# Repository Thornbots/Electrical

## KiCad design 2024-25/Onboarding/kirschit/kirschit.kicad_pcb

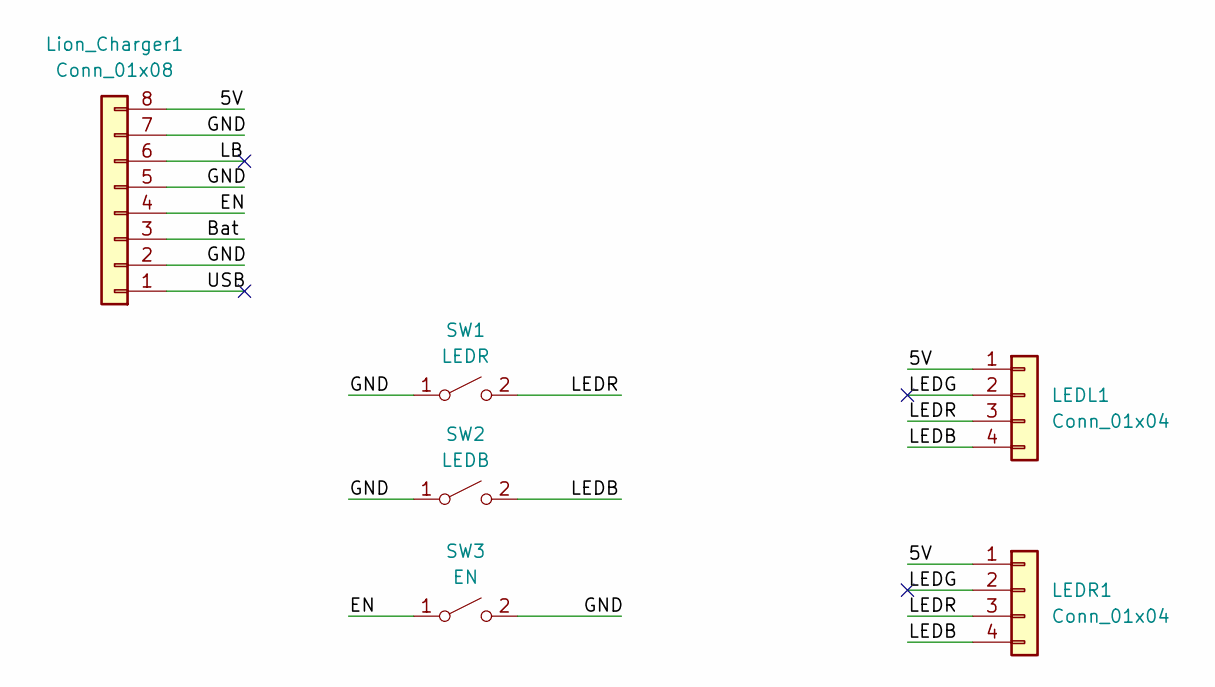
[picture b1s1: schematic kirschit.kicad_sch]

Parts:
LEDL1: Conn_01x04; PinSocket_1x04_P2.54mm_Vertical
LEDR1: Conn_01x04; PinSocket_1x04_P2.54mm_Vertical
Lion_Charger1: Conn_01x08; PinSocket_1x08_P2.54mm_Vertical
SW1: LEDR; SW_RB141C1100
SW2: LEDB; SW_RB141C1100
SW3: EN; SW_RB141C1100

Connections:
/5V: LEDL1.1, LEDR1.1, Lion_Charger1.8
/Bat: Lion_Charger1.3
/EN: Lion_Charger1.4, SW3.1 (A)
/GND: Lion_Charger1.2, Lion_Charger1.5, Lion_Charger1.7, SW1.1 (A), SW2.1 (A), SW3.2 (B)
/LB: Lion_Charger1.6
/LEDB: LEDL1.4, LEDR1.4, SW2.2 (B)
/LEDG: LEDL1.2, LEDR1.2
/LEDR: LEDL1.3, LEDR1.3, SW1.2 (B)
/USB: Lion_Charger1.1

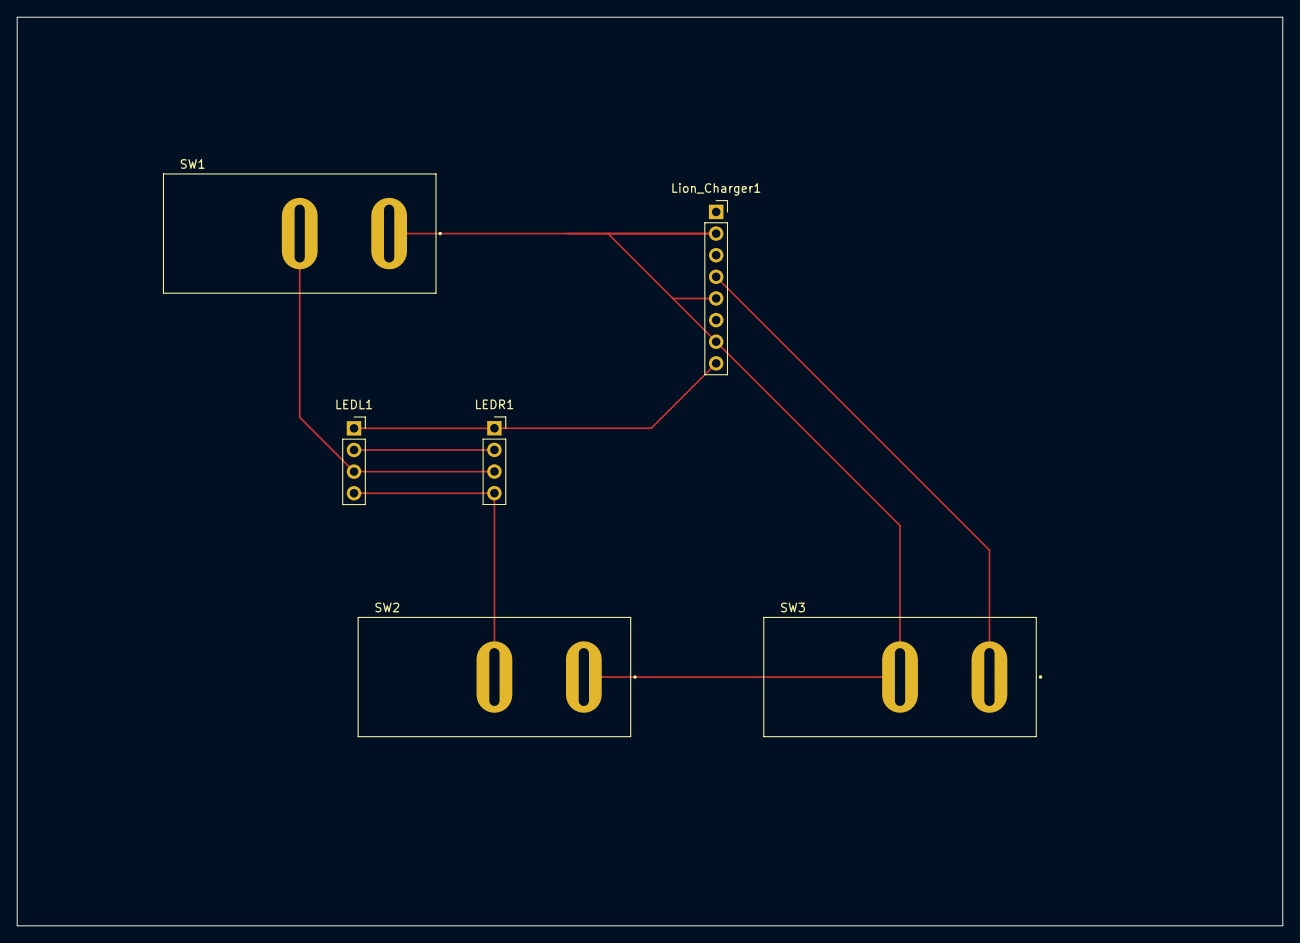
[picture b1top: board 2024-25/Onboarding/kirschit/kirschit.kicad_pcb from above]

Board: 2 copper layers, 148.6 x 106.7 mm, 6 parts (0 on the bottom side), 6 nets.

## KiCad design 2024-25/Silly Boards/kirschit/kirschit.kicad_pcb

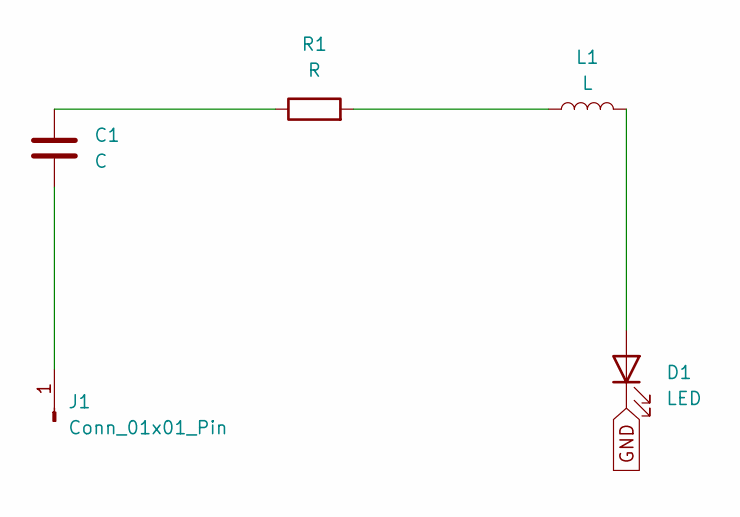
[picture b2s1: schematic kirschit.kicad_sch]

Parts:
C1: C; C_Elec_3x5.4
D1: LED; LED_D3.0mm_Horizontal_O3.81mm_Z6.0mm
J1: Conn_01x01_Pin; PinHeader_1x01_P2.54mm_Vertical
L1: L; L_Axial_L5.3mm_D2.2mm_P7.62mm_Horizontal_Vishay_IM-1
R1: R; R_Axial_DIN0414_L11.9mm_D4.5mm_P15.24mm_Horizontal

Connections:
GND: D1.1 (K)
unnamed: C1.1, R1.1
unnamed: D1.2 (A), L1.2
unnamed: C1.2, J1.1
unnamed: L1.1, R1.2

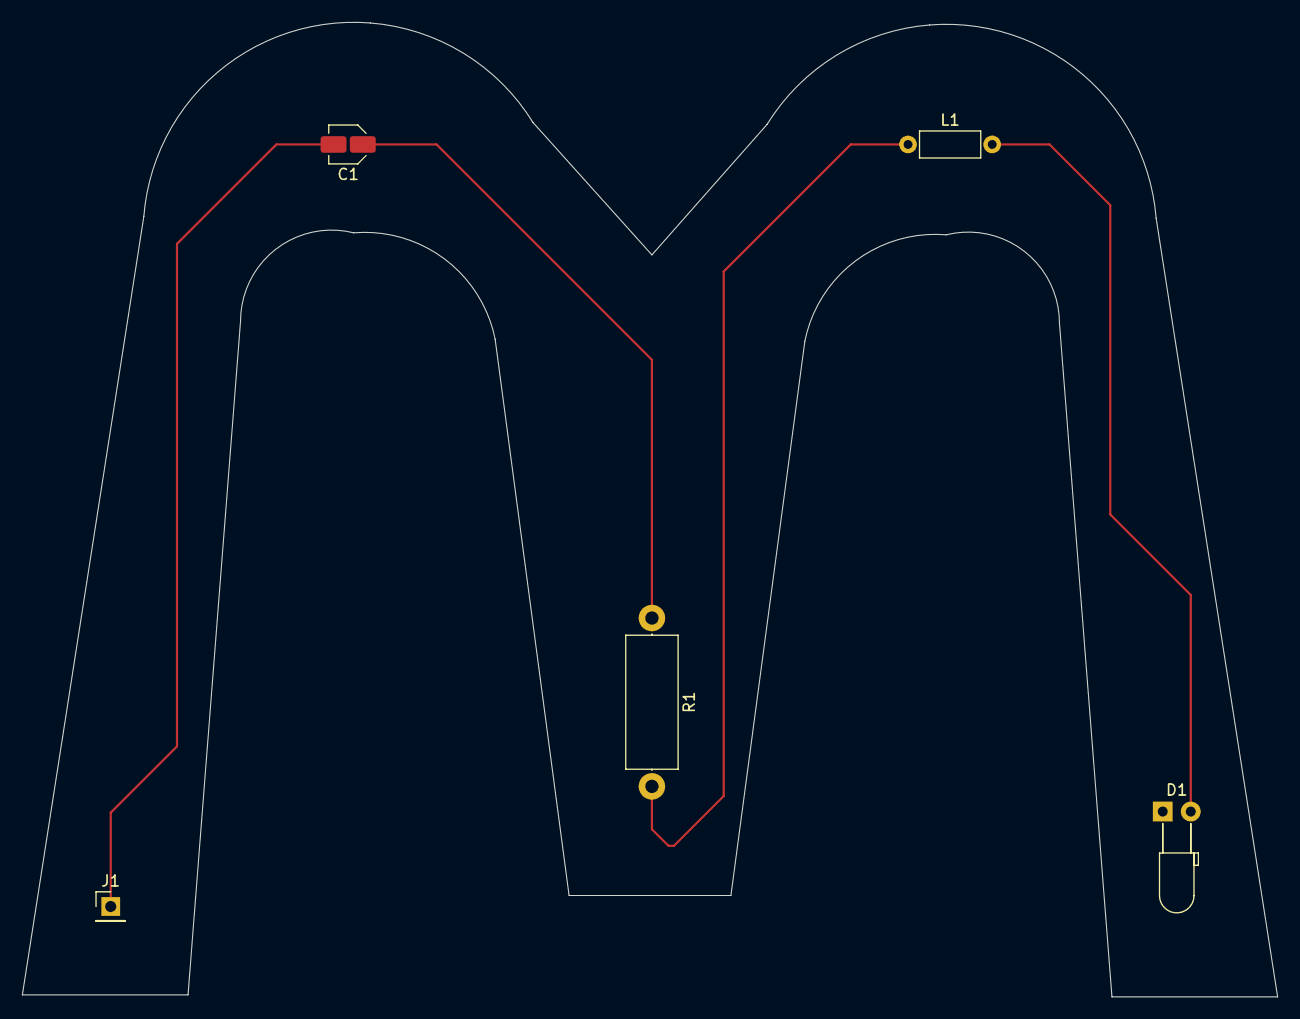
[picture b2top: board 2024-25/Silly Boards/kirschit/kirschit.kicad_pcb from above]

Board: 2 copper layers, 113.7 x 88.2 mm, 5 parts (0 on the bottom side), 4 nets.

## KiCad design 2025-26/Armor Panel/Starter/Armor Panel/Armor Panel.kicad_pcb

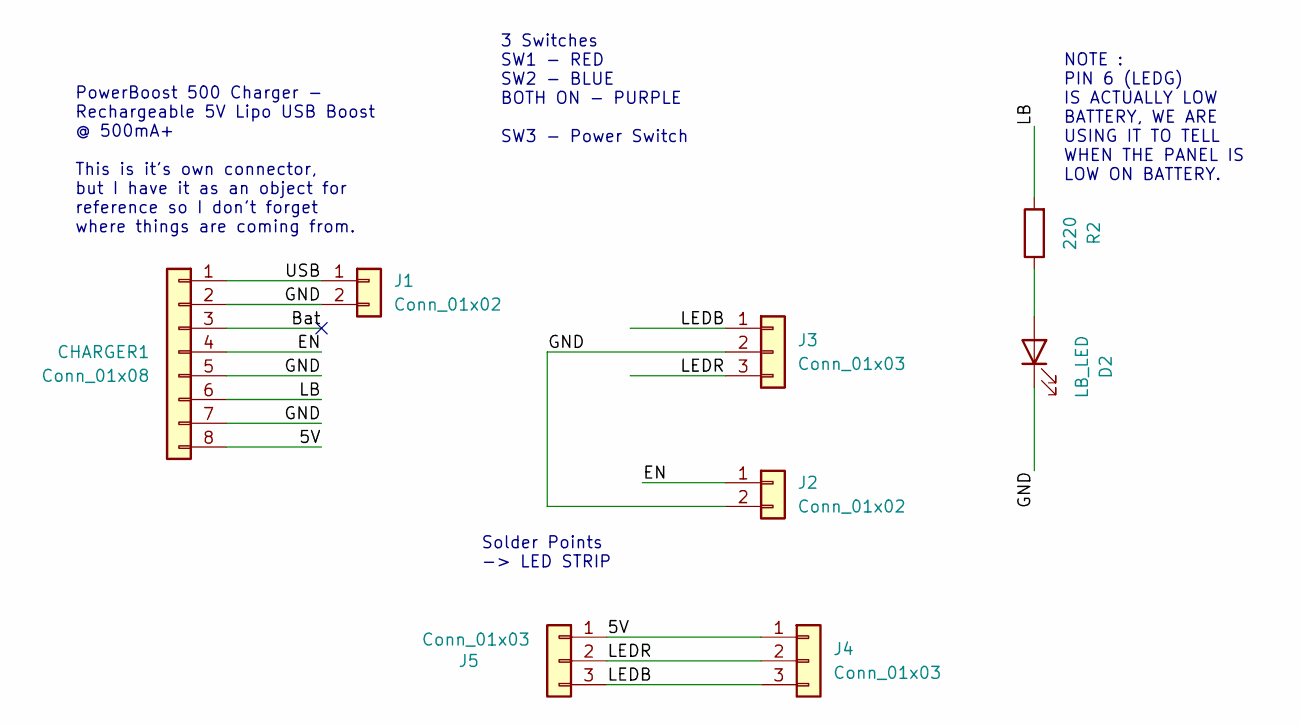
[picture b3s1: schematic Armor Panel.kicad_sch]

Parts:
CHARGER1: Conn_01x08; Power Boost Board
D2: LB_LED; LED_D5.0mm
J1, J2: Conn_01x02; JST_PH_B2B-PH-K_1x02_P2.00mm_Vertical
J3, J4, J5: Conn_01x03; JST_PH_B3B-PH-K_1x03_P2.00mm_Vertical
R2: 220; R_Axial_DIN0309_L9.0mm_D3.2mm_P12.70mm_Horizontal

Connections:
/5V: CHARGER1.8, J4.1, J5.1
/Bat: CHARGER1.3
/EN: CHARGER1.4, J2.1
/GND: CHARGER1.2, CHARGER1.5, CHARGER1.7, D2.1 (K), J1.2, J2.2, J3.2
/LB: CHARGER1.6, R2.2
/LEDB: J3.1, J4.3, J5.3
/LEDR: J3.3, J4.2, J5.2
/USB: CHARGER1.1, J1.1
unnamed: D2.2 (A), R2.1

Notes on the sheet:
PowerBoost 500 Charger - Rechargeable 5V Lipo USB Boost @ 500mA+ This is it's own connector, but I have it as an object for reference so I don't forget where things are coming from.
Solder Points -> LED STRIP
3 Switches SW1 - RED SW2 - BLUE BOTH ON - PURPLE SW3 - Power Switch
NOTE : PIN 6 (LEDG) IS ACTUALLY LOW BATTERY, WE ARE USING IT TO TELL WHEN THE PANEL IS LOW ON BATTERY.

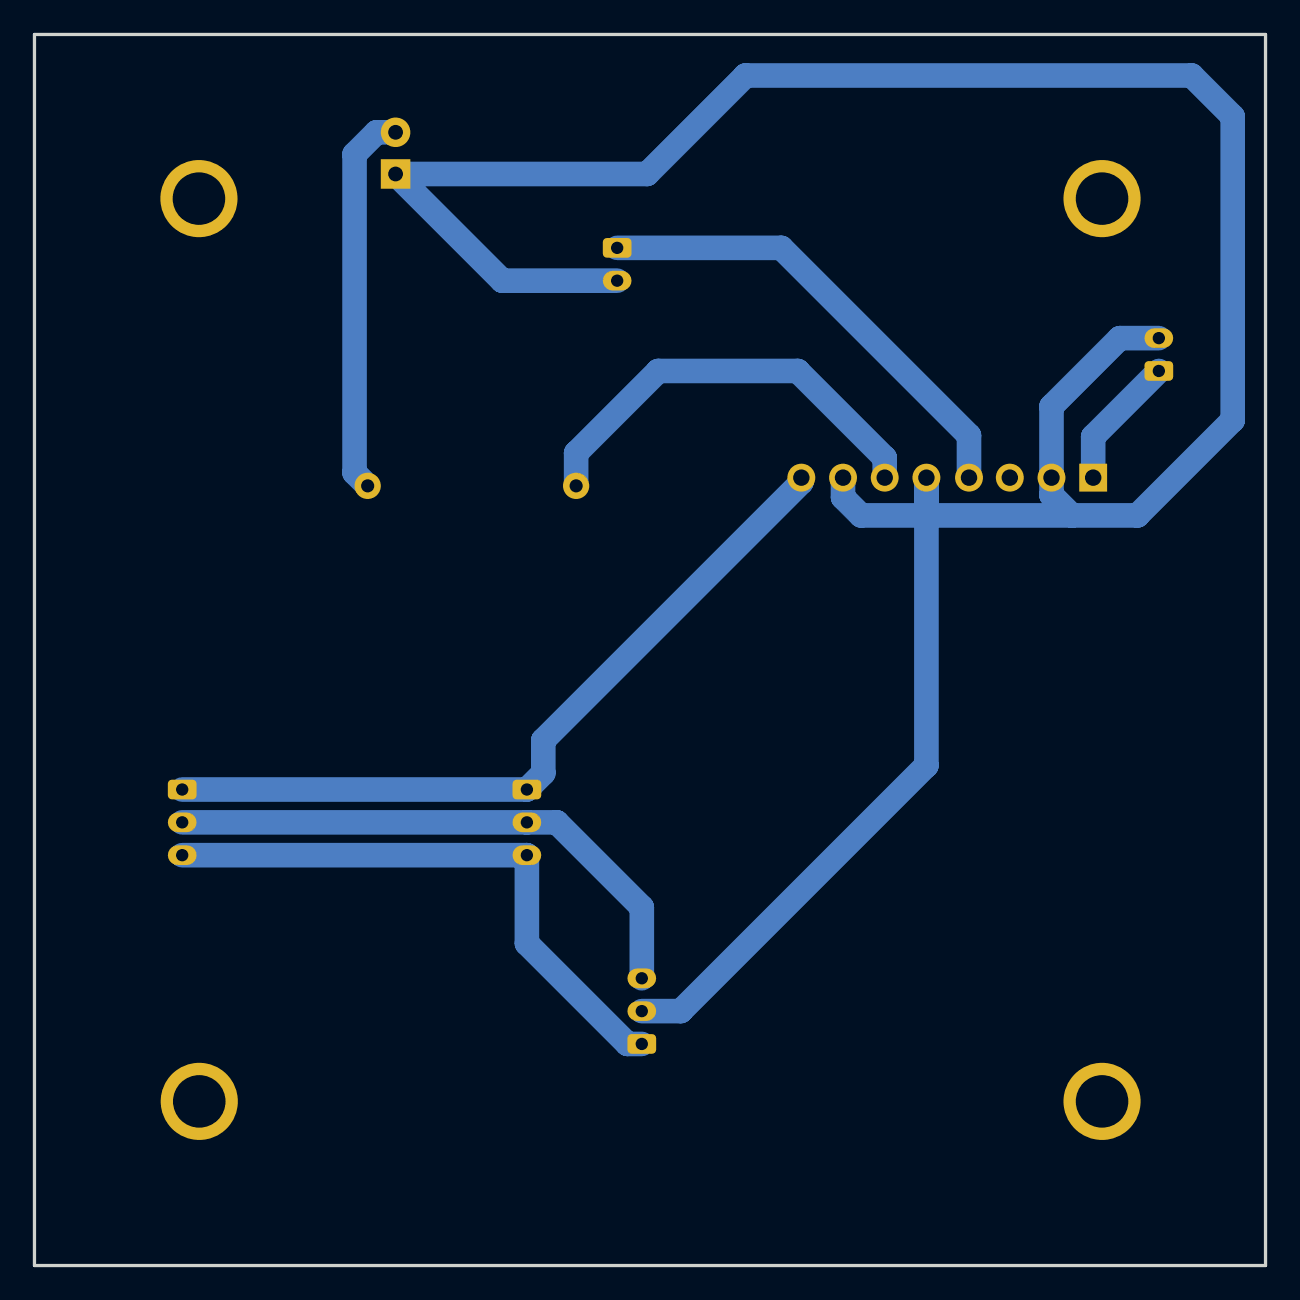
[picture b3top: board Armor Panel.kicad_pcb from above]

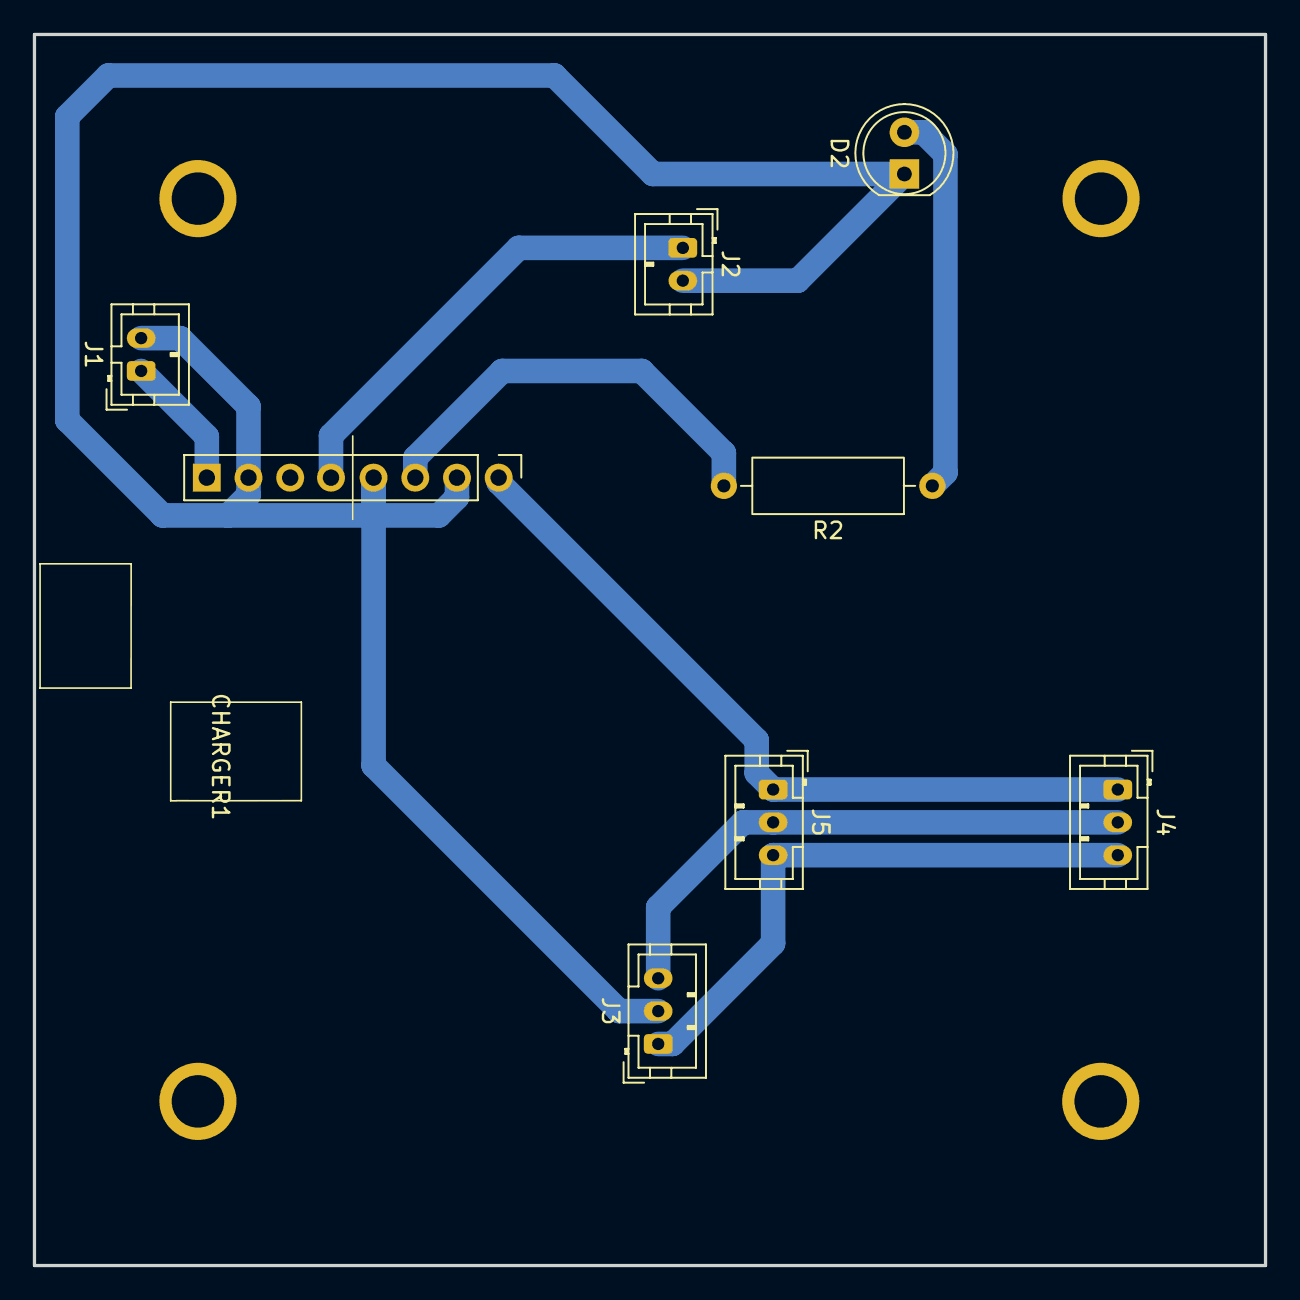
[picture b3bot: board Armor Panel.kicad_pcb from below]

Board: 2 copper layers, 75.0 x 75.0 mm, 8 parts (8 on the bottom side), 8 nets.

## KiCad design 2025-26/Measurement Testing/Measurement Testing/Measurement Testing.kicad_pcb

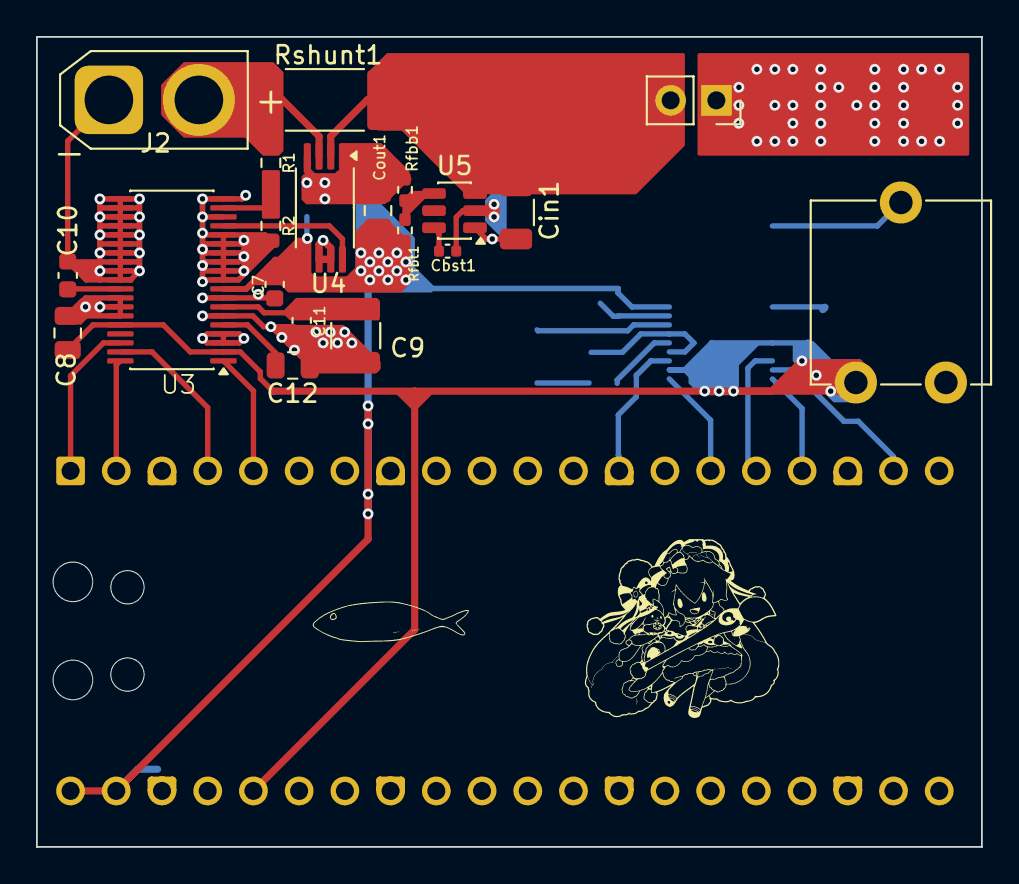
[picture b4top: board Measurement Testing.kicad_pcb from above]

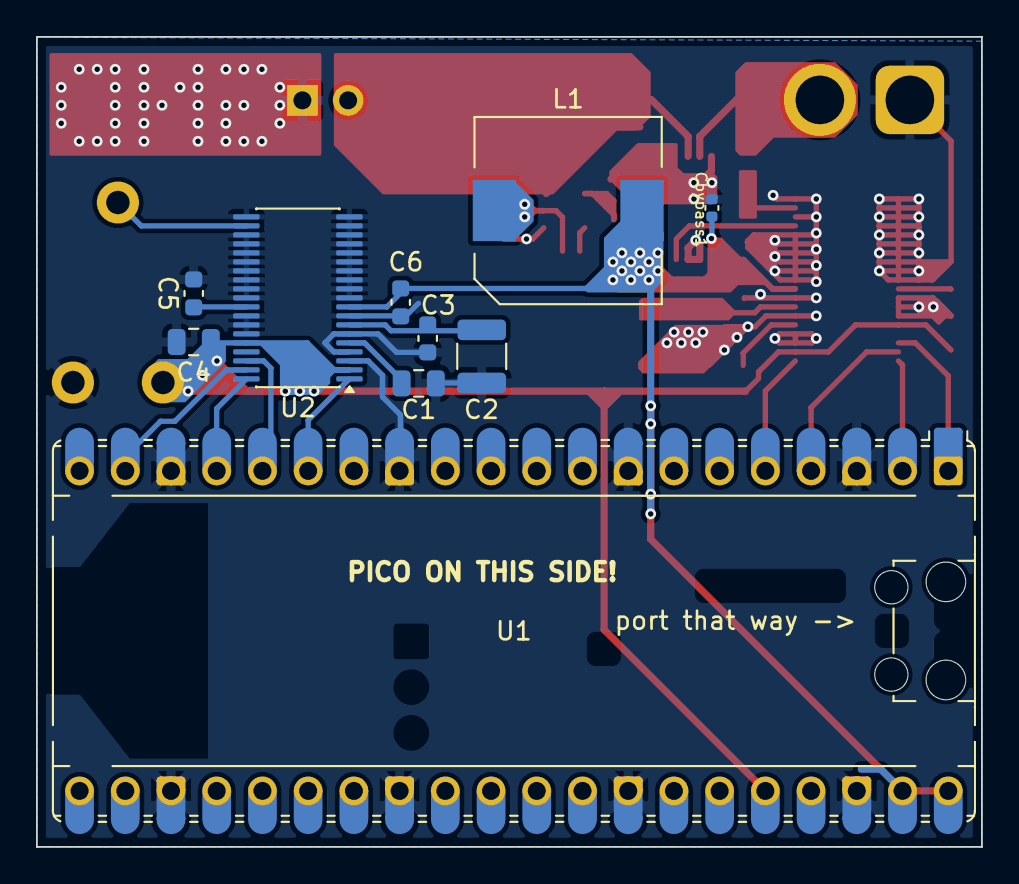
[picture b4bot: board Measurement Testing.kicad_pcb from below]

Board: 2 copper layers, 52.5 x 45.0 mm, 30 parts (10 on the bottom side), 25 nets.

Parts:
C1, C4, C8, C12: 10 uF; C_0805_2012Metric
C2, C9: 22 uF; C_1210_3225Metric
C3, C5, C6, C7, C10, C11: 1 uF; C_0603_1608Metric
Cbst1: 100n; C_0402_1005Metric
Cbypass1: 100n; C_0402_1005Metric
Cin1: 10u; C_1206_3216Metric
Cout1: 47u; C_0805_2012Metric
J1: Power Supply; PinSocket_1x02_P2.54mm_Vertical
J2: XT30PW-F; AMASS_XT30U-F_1x02_P5.0mm_Vertical
L1: 13u; L_Wuerth_WE-PDF
R1: 8.2k; R_0603_1608Metric
R2: 1k; R_0603_1608Metric
RV1: R_Potentiometer; Potentiometer_ACP_CA9-V10_Vertical
Rfbb1: 13.7k; R_0402_1005Metric_Pad0.72x0.64mm_HandSolder
Rfbt1: 100k; R_0402_1005Metric_Pad0.72x0.64mm_HandSolder
Rshunt1: 5m; R_2512_6332Metric
U1: RASPBERRY_PI_PICO; RaspberryPi_Pico_Common_Unspecified
U2, U3: ADS8684IDBTR; TSSOP-38_4.4x9.7mm_P0.5mm
U4: INA240A2PWR; TSSOP-8_4.4x3mm_P0.65mm
U5: TPS54308DDCR; SOT-23-6

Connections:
3V3: C4.1, C8.1, RV1.3, U1.36 (3V3), U2.2 (~RST/~PD), U2.34 (DVDD), U3.2 (~RST/~PD), U3.34 (DVDD)
5V: C6.1, C7.1, Cbypass1.2, Cout1.1, L1.2, Rfbt1.1, U1.39 (VSYS), U1.40 (VBUS), U2.9 (AVDD), U3.9 (AVDD), U4.5
GND: C1.2, C2.2, C3.2, C4.2, C5.2, C6.2, C7.2, C8.2, C9.2, C10.2, C11.2, C12.2, Cbypass1.1, Cin1.2, Cout1.2, J1.1, J2.1, R2.2, RV1.1, Rfbb1.2, U1.3 (GND), U1.8 (GND), U1.13 (GND), U1.18 (GND), U1.23 (GND), U1.28 (GND), U1.33 (AGND), U1.38 (GND), U2.3 (DAISY), U2.4 (~REFSEL), U2.6 (REFGND), U2.8 (AGND), U2.10 (AUX_IN), U2.11 (AUX_GND), U2.12 (NC), U2.13 (NC__1), U2.14 (NC__2), U2.15 (NC__3), U2.16 (AIN_0P), U2.17 (AIN_0GND), U2.18 (AIN_1P), U2.19 (AIN_1GND), U2.20 (AIN_2GND), U2.22 (AIN_3GND), U2.23 (AIN_3P), U2.24 (NC__4), U2.25 (NC__5), U2.26 (NC__6), U2.27 (NC__7), U2.28 (AGND__1), U2.29 (AGND__2), U2.31 (AGND__3), U2.32 (AGND__4), U2.33 (DGND), U3.3 (DAISY), U3.4 (~REFSEL), U3.6 (REFGND), U3.8 (AGND), U3.10 (AUX_IN), U3.11 (AUX_GND), U3.12 (NC), U3.13 (NC__1), U3.14 (NC__2), U3.15 (NC__3), U3.17 (AIN_0GND), U3.19 (AIN_1GND), U3.20 (AIN_2GND), U3.21 (AIN_2P), U3.22 (AIN_3GND), U3.23 (AIN_3P), U3.24 (NC__4), U3.25 (NC__5), U3.26 (NC__6), U3.27 (NC__7), U3.28 (AGND__1), U3.29 (AGND__2), U3.31 (AGND__3), U3.32 (AGND__4), U3.33 (DGND), U4.1, U4.4, U4.6, U4.7, U5.1 (GND)
unnamed: J2.2, R1.1, Rshunt1.2, U4.3
unnamed: U1.1 (GPIO0), U3.36 (SDO)
unnamed: U1.2 (GPIO1), U3.38 (~CS)
unnamed: U1.4 (GPIO2), U3.37 (SCLK)
unnamed: U1.5 (GPIO3), U3.1 (SDI)
unnamed: U1.15 (GPIO11), U2.1 (SDI)
unnamed: U1.16 (GPIO12), U2.36 (SDO)
unnamed: U1.17 (GPIO13), U2.38 (~CS)
unnamed: U1.19 (GPIO14), U2.37 (SCLK)
unnamed: RV1.2, U2.21 (AIN_2P)
unnamed: C5.1, U2.30 (AVDD__1)
unnamed: C2.1, C3.1, U2.7 (REFCAP)
unnamed: C1.1, U2.5 (REFIO)
unnamed: U3.16 (AIN_0P), U4.8
unnamed: R1.2, R2.1, U3.18 (AIN_1P)
unnamed: C10.1, U3.30 (AVDD__1)
unnamed: C9.1, C11.1, U3.7 (REFCAP)
unnamed: C12.1, U3.5 (REFIO)
unnamed: Cbst1.1, U5.6 (BOOT)
unnamed: Rfbb1.1, Rfbt1.2, U5.4 (FB)
unnamed: Cbst1.2, L1.1, U5.2 (SW)
VIN: Cin1.1, J1.2, Rshunt1.1, U4.2, U5.3 (VIN)

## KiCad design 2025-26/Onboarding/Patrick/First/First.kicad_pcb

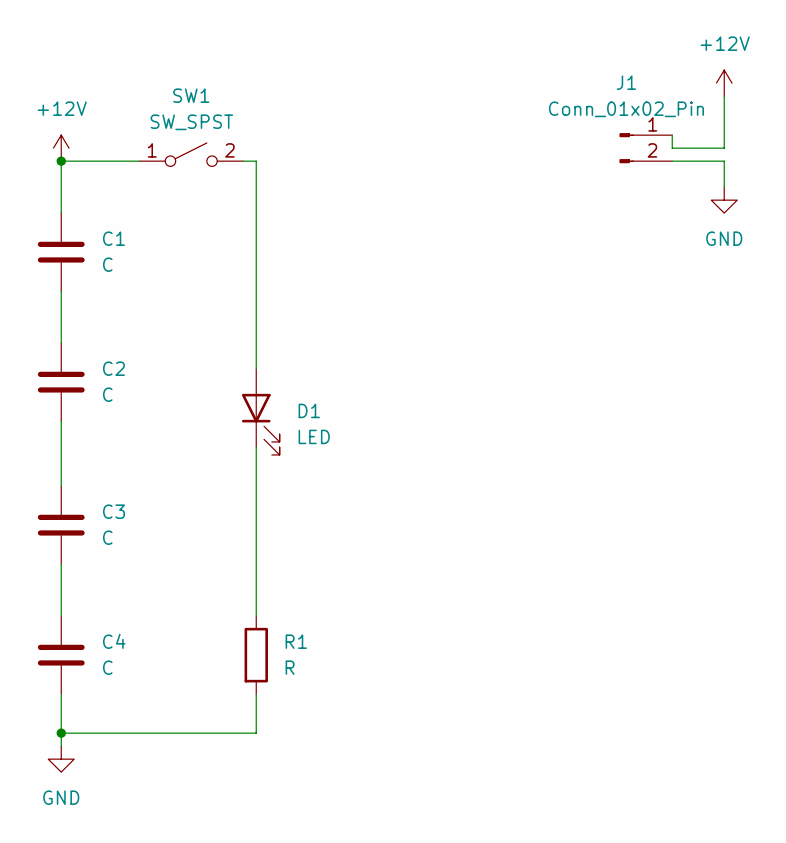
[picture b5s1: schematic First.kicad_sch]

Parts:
C1, C2, C3, C4: C; SupeCapacitor Through Hole
D1: LED; LED Through Hole
J1: Conn_01x02_Pin; XT30PW-F
R1: R; Through Hole Resistor
SW1: SW_SPST; SPST Through Hole Switch

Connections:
+12V: C1.1, J1.1, SW1.1 (A)
GND: C4.2, J1.2, R1.2
unnamed: C1.2, C2.1
unnamed: C2.2, C3.1
unnamed: C3.2, C4.1
unnamed: D1.2 (A), SW1.2 (B)
unnamed: D1.1 (K), R1.1

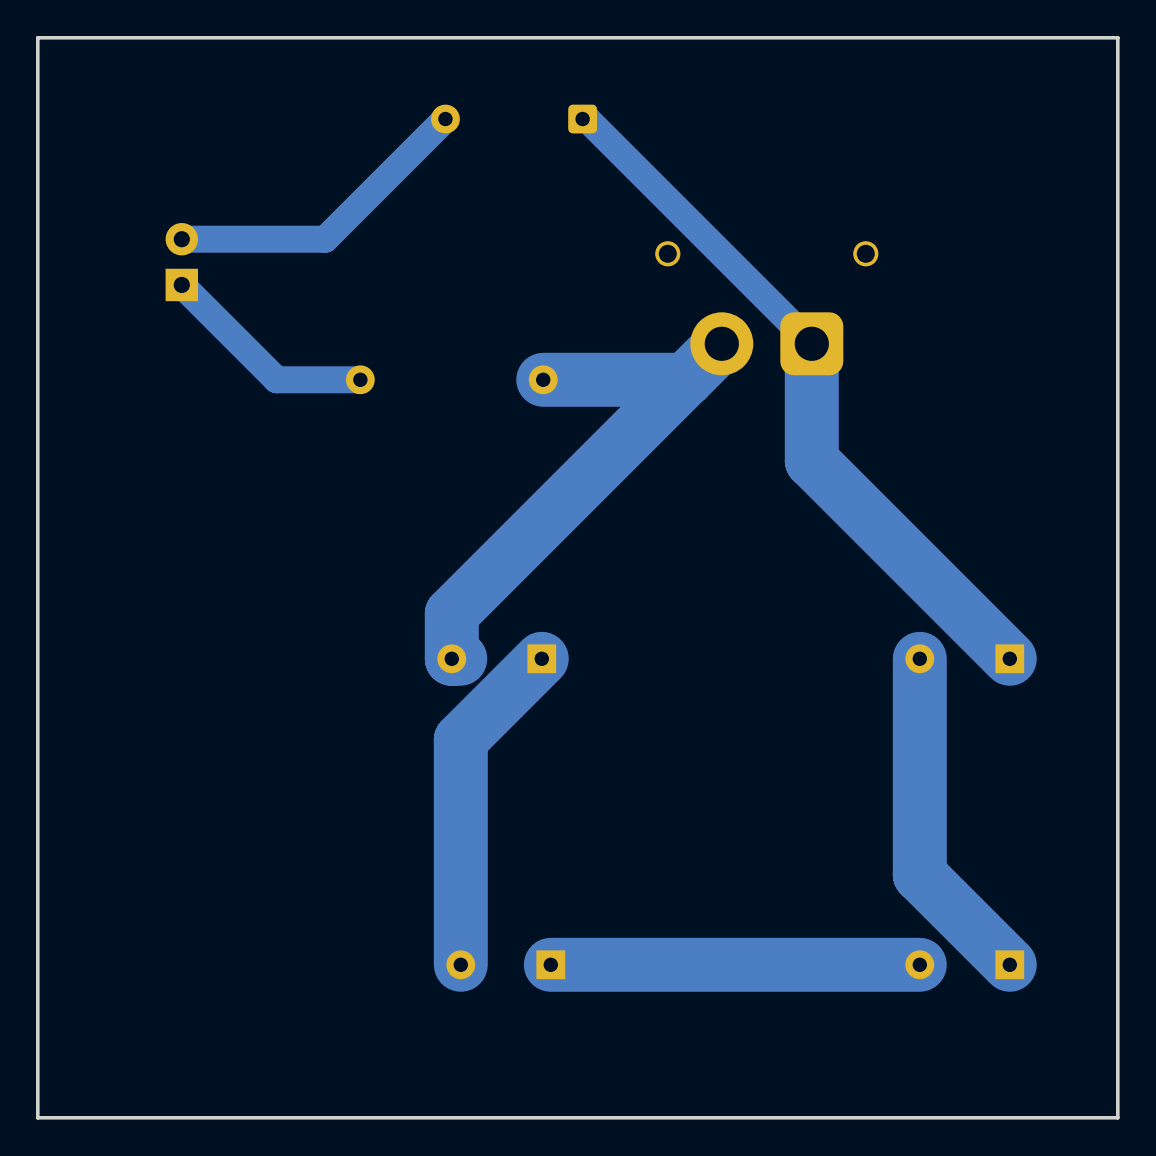
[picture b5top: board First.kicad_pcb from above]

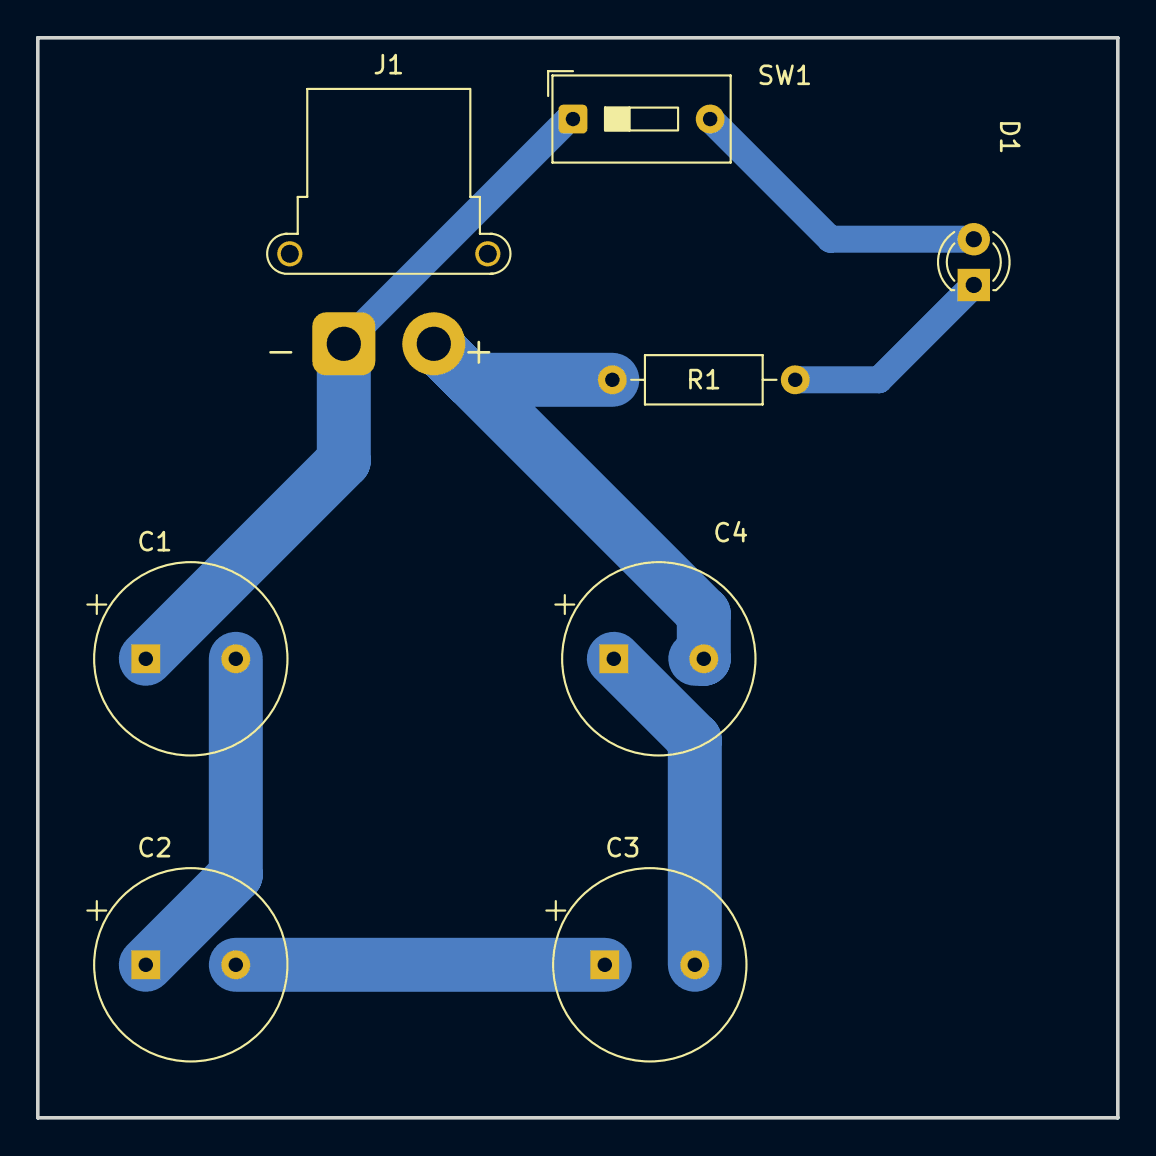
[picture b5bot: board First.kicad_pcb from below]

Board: 2 copper layers, 60.0 x 60.0 mm, 8 parts (8 on the bottom side), 7 nets.
